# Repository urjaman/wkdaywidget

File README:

The Weekday-o-matic aka wkdaywidget
-----------------------------------

This is a rather gigantic "Arduino" shield,
to make a rather big display showing the
current day of week. Or well atleast the
firmware for running it and a design
for the PCB on it.

BOM for the whole thing:
- An ATmega328-based arduino (Uno R3 clone)
- A DS1307 RTC module (with backup battery) soldered into the arduino I2C pins
	(or a datalogger shield, do not insert an SD card to that tho)
- the PCB (in hw-kicad/)
- some 0.1" headers
- 2 big common cathode 16-segment displays:
https://www.ebay.com/itm/2-3-16Segment-1-Digit-Bit-RED-LED-Display-Red-Signs-2-3inch-16-segment-CC-CA/254326426921

- 4 SO-16 74HC595D shift register & latches
- 5 4x0603 100ohm resistor arrays (RN1, RN2, RN4, RN5, RN7)
- 3 4x0603 220ohm resistor arrays (RN3, RN6, RN8)
- 2 560ohm 0603 resistors
- 1 100kohm 0603 resistor
- 4 0.1uF 0603 capacitors
- 2 "6mm" "standard" PCB push buttons

NOTE/WARNING: in the current PCB the spacing between the rows on the big displays is too big (tall, whatever),
though it was possible to bend the pins on the display enough to push them in.

If you intend to build this, i recommend you first get the displays and measure 
the actual row spacing (because i did it to the spec on ebay, 62mm, but no dice)
and adjust the PCB design appropriately (or email me for me to do that).
I'd do it but I already soldered my displays down (so hard to measure) + am lazy.
(This is mostly a note to self in case i ever get more PCBs :P)

The firmware defaults to finnish, but just adjust the includes 
in the beginning of ui.c to get english.

PRs accepted if you want to add a header for your own language :)

To clone this repo, remember to use --recursive since it contains a submodule.
You will need an AVR toolchain (avr-gcc, avr-libc etc) to build the firmware,
and avrdude to program it.

The targets are just "make" to build the firmware and "make program" for the
programming. Check the Makefile that you have the correct serial device
etc first.

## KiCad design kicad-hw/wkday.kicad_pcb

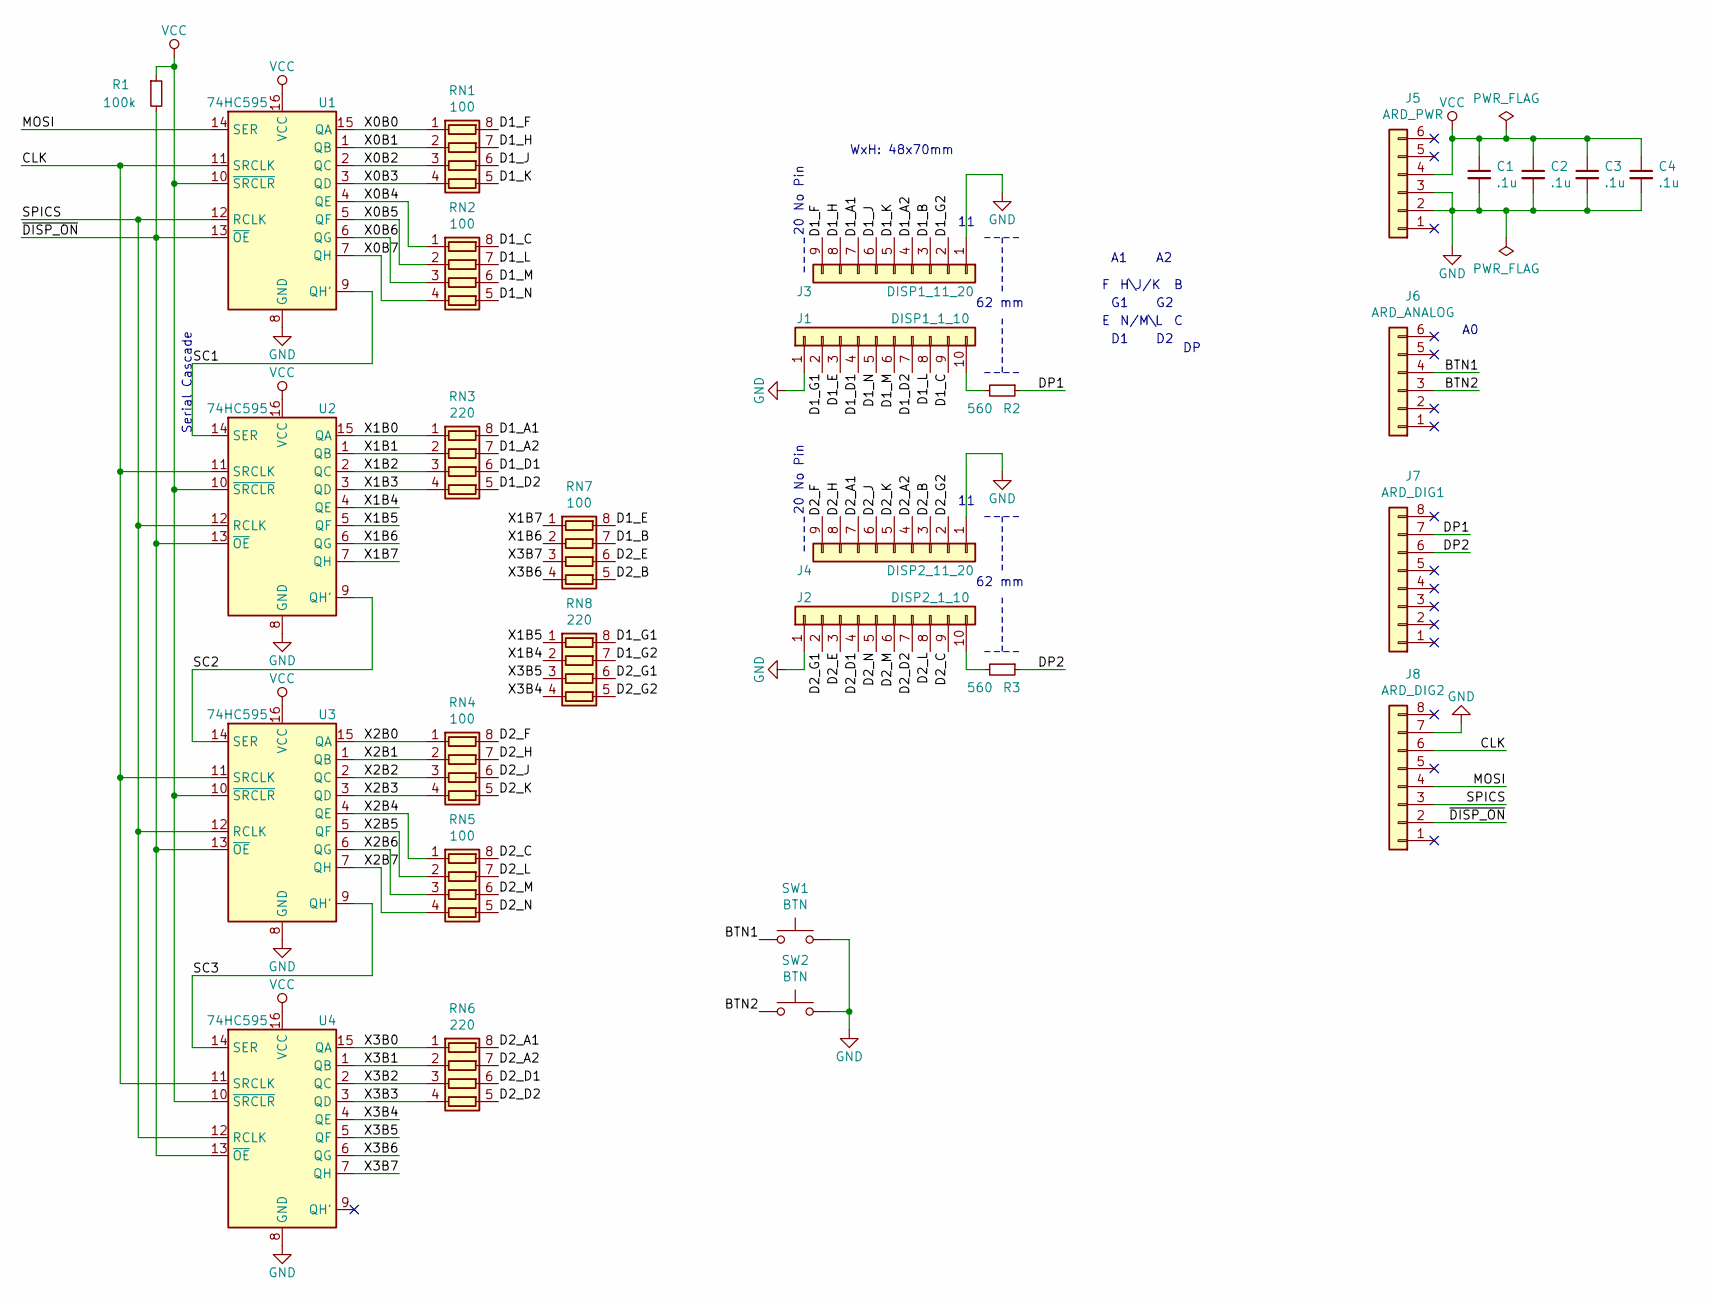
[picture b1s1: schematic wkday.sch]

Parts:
C1, C2, C3, C4: .1u; C_0603_1608Metric_Pad1.05x0.95mm_HandSolder
J1: DISP1_1_10; PinHeader_1x10_P2.54mm_Vertical
J2: DISP2_1_10; PinHeader_1x10_P2.54mm_Vertical
J3: DISP1_11_20; PinHeader_1x09_P2.54mm_Vertical
J4: DISP2_11_20; PinHeader_1x09_P2.54mm_Vertical
J5: ARD_PWR; PinHeader_1x06_P2.54mm_Vertical
J6: ARD_ANALOG; PinHeader_1x06_P2.54mm_Vertical
J7: ARD_DIG1; PinHeader_1x08_P2.54mm_Vertical
J8: ARD_DIG2; PinHeader_1x08_P2.54mm_Vertical
R1: 100k; R_0603_1608Metric_Pad1.05x0.95mm_HandSolder
R2, R3: 560; R_0603_1608Metric_Pad1.05x0.95mm_HandSolder
RN1, RN2, RN4, RN5, RN7: 100; R_Array_Concave_4x0603
RN3, RN6, RN8: 220; R_Array_Concave_4x0603
SW1, SW2: BTN; SW_PUSH_6mm
U1, U2, U3, U4: 74HC595; SOIC-16_3.9x9.9mm_P1.27mm

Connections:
/BTN1: J6.4, SW1.1
/BTN2: J6.3, SW2.1
/CLK: J8.6, U1.11 (SRCLK), U2.11 (SRCLK), U3.11 (SRCLK), U4.11 (SRCLK)
/D1_A1: J3.7, RN3.8 (R1.2)
/D1_A2: J3.4, RN3.7 (R2.2)
/D1_B: J3.3, RN7.7 (R2.2)
/D1_C: J1.9, RN2.8 (R1.2)
/D1_D1: J1.4, RN3.6 (R3.2)
/D1_D2: J1.7, RN3.5 (R4.2)
/D1_E: J1.3, RN7.8 (R1.2)
/D1_F: J3.9, RN1.8 (R1.2)
/D1_G1: J1.2, RN8.8 (R1.2)
/D1_G2: J3.2, RN8.7 (R2.2)
/D1_H: J3.8, RN1.7 (R2.2)
/D1_J: J3.6, RN1.6 (R3.2)
/D1_K: J3.5, RN1.5 (R4.2)
/D1_L: J1.8, RN2.7 (R2.2)
/D1_M: J1.6, RN2.6 (R3.2)
/D1_N: J1.5, RN2.5 (R4.2)
/D2_A1: J4.7, RN6.8 (R1.2)
/D2_A2: J4.4, RN6.7 (R2.2)
/D2_B: J4.3, RN7.5 (R4.2)
/D2_C: J2.9, RN5.8 (R1.2)
/D2_D1: J2.4, RN6.6 (R3.2)
/D2_D2: J2.7, RN6.5 (R4.2)
/D2_E: J2.3, RN7.6 (R3.2)
/D2_F: J4.9, RN4.8 (R1.2)
/D2_G1: J2.2, RN8.6 (R3.2)
/D2_G2: J4.2, RN8.5 (R4.2)
/D2_H: J4.8, RN4.7 (R2.2)
/D2_J: J4.6, RN4.6 (R3.2)
/D2_K: J4.5, RN4.5 (R4.2)
/D2_L: J2.8, RN5.7 (R2.2)
/D2_M: J2.6, RN5.6 (R3.2)
/D2_N: J2.5, RN5.5 (R4.2)
/DP1: J7.7, R2.1
/DP2: J7.6, R3.1
/MOSI: J8.4, U1.14 (SER)
/SC1: U1.9 (QH'), U2.14 (SER)
/SC2: U2.9 (QH'), U3.14 (SER)
/SC3: U3.9 (QH'), U4.14 (SER)
/SPICS: J8.3, U1.12 (RCLK), U2.12 (RCLK), U3.12 (RCLK), U4.12 (RCLK)
/X0B0: RN1.1 (R1.1), U1.15 (QA)
/X0B1: RN1.2 (R2.1), U1.1 (QB)
/X0B2: RN1.3 (R3.1), U1.2 (QC)
/X0B3: RN1.4 (R4.1), U1.3 (QD)
/X0B4: RN2.1 (R1.1), U1.4 (QE)
/X0B5: RN2.2 (R2.1), U1.5 (QF)
/X0B6: RN2.3 (R3.1), U1.6 (QG)
/X0B7: RN2.4 (R4.1), U1.7 (QH)
/X1B0: RN3.1 (R1.1), U2.15 (QA)
/X1B1: RN3.2 (R2.1), U2.1 (QB)
/X1B2: RN3.3 (R3.1), U2.2 (QC)
/X1B3: RN3.4 (R4.1), U2.3 (QD)
/X1B4: RN8.2 (R2.1), U2.4 (QE)
/X1B5: RN8.1 (R1.1), U2.5 (QF)
/X1B6: RN7.2 (R2.1), U2.6 (QG)
/X1B7: RN7.1 (R1.1), U2.7 (QH)
/X2B0: RN4.1 (R1.1), U3.15 (QA)
/X2B1: RN4.2 (R2.1), U3.1 (QB)
/X2B2: RN4.3 (R3.1), U3.2 (QC)
/X2B3: RN4.4 (R4.1), U3.3 (QD)
/X2B4: RN5.1 (R1.1), U3.4 (QE)
/X2B5: RN5.2 (R2.1), U3.5 (QF)
/X2B6: RN5.3 (R3.1), U3.6 (QG)
/X2B7: RN5.4 (R4.1), U3.7 (QH)
/X3B0: RN6.1 (R1.1), U4.15 (QA)
/X3B1: RN6.2 (R2.1), U4.1 (QB)
/X3B2: RN6.3 (R3.1), U4.2 (QC)
/X3B3: RN6.4 (R4.1), U4.3 (QD)
/X3B4: RN8.4 (R4.1), U4.4 (QE)
/X3B5: RN8.3 (R3.1), U4.5 (QF)
/X3B6: RN7.4 (R4.1), U4.6 (QG)
/X3B7: RN7.3 (R3.1), U4.7 (QH)
/~DISP_ON: J8.2, R1.2, U1.13 (~OE), U2.13 (~OE), U3.13 (~OE), U4.13 (~OE)
GND: C1.2, C2.2, C3.2, C4.2, J1.1, J2.1, J3.1, J4.1, J5.2, J5.3, J8.7, SW1.2, SW2.2, U1.8 (GND), U2.8 (GND), U3.8 (GND), U4.8 (GND)
unnamed: J1.10, R2.2
unnamed: J2.10, R3.2
VCC: C1.1, C2.1, C3.1, C4.1, J5.4, R1.1, U1.10 (~SRCLR), U1.16 (VCC), U2.10 (~SRCLR), U2.16 (VCC), U3.10 (~SRCLR), U3.16 (VCC), U4.10 (~SRCLR), U4.16 (VCC)

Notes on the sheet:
62 mm
20 No Pin
H\J/K
N/M\L
Serial Cascade
WxH: 48x70mm

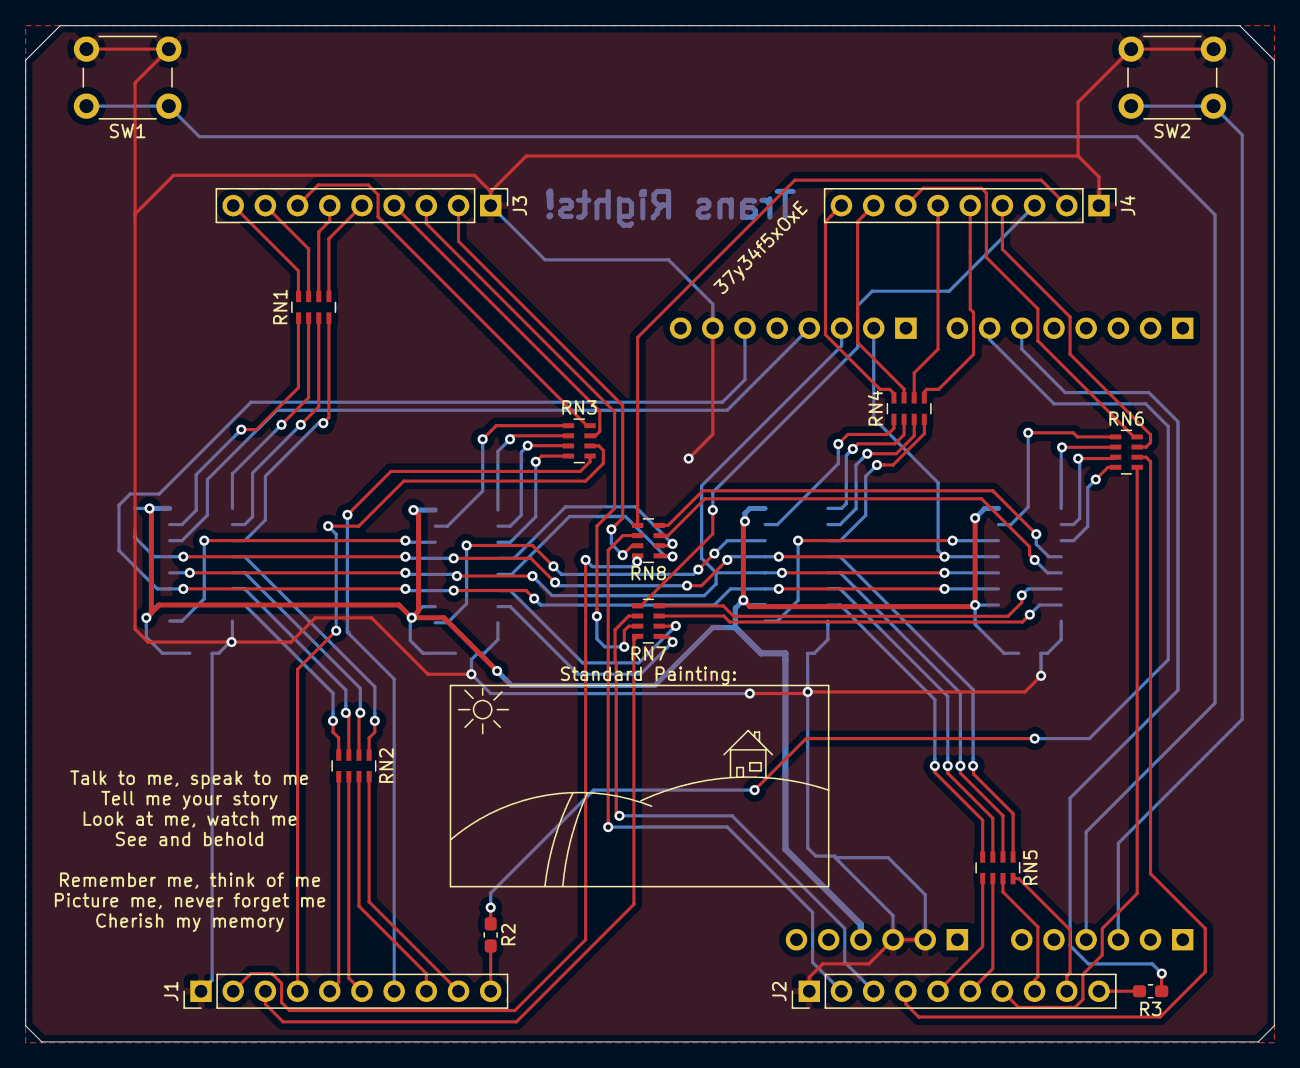
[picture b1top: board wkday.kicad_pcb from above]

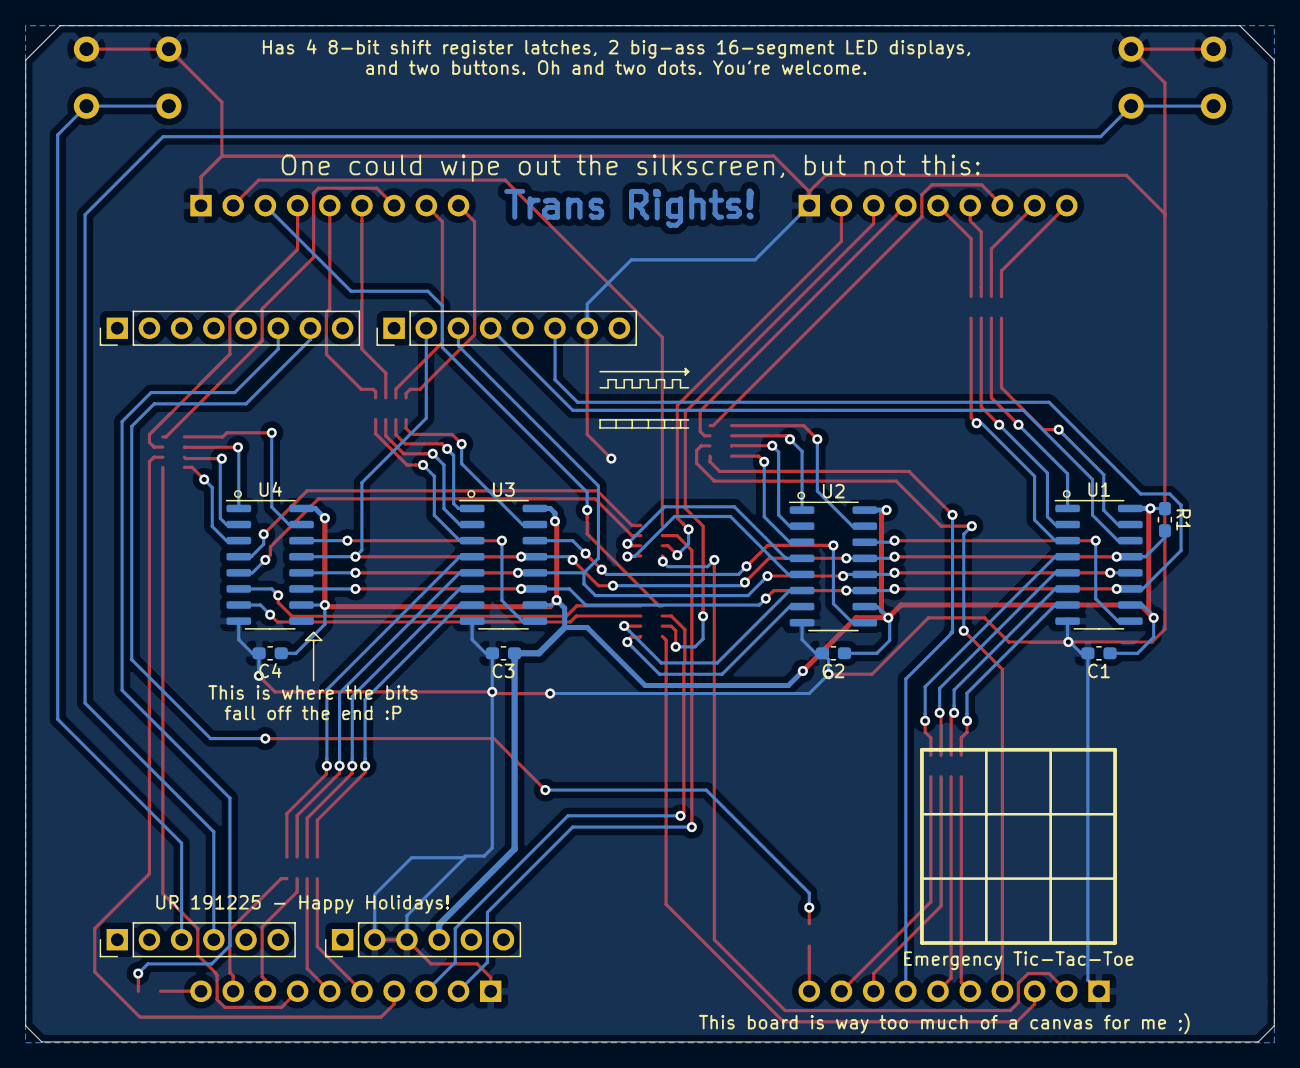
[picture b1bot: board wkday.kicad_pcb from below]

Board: 2 copper layers, 98.5 x 80.2 mm, 29 parts (13 on the bottom side), 79 nets.

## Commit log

2020-01-29 Initial set of files for wkdaysw
    These are based on my work with datalogger/logadatter :P
2020-01-29 Add ciface and the first functional 16-segment display driving code
2020-01-30 First UI
2020-01-31 More symbols, even if they're of questionale understanding
2020-01-31 Add ability to use the RTC NVRAM for a settings "blob"
2020-01-31 UI work WIP
2020-01-31 Make the 1hzp hit once right after init routines
    This cleans up the boot so that all "once a second" actions
    are done immediately
2020-01-31 Add menu and brightness control ability
2020-01-31 Show the brightness as you're adjusting it
    user friendlyness(TM)
2020-01-31 save the RAM, oh will ya save the RAM ...
2020-02-01 Do as much power mgmt as we need on this thing
    Just idle the AVR, and remove the "system idle" management of the datalogger
    ("system idle" was for deep sleeping)
2020-02-01 Move the finnish bits into a language header
2020-02-01 Add a missing wait_nokey on time set complete
    also cleanup a little
2020-02-01 Add the english language option :)
2020-02-01 Oops make the time set actually set the time you wanted
    It wasnt clearing the seconds so it'd set some random moment
    on the specified minute, not the 0 point...
2020-02-01 Add the kicad PCB design that goes with this (also gitignore)
2020-02-01 cleanup and add GPL headers
2020-02-01 Unify header style
2020-02-01 Add a README
2020-02-01 Add some renders for the masses to enjoy
2023-01-29 A quick hack'n'slash for an RV-3032-C7
    Using the RTC module from bikeoledsw as-is.
    Not that we need 3.6864Mhz, but it doesnt hurt, and the
    setup should be otherwise compatible (a CR1220 in a holder.)
